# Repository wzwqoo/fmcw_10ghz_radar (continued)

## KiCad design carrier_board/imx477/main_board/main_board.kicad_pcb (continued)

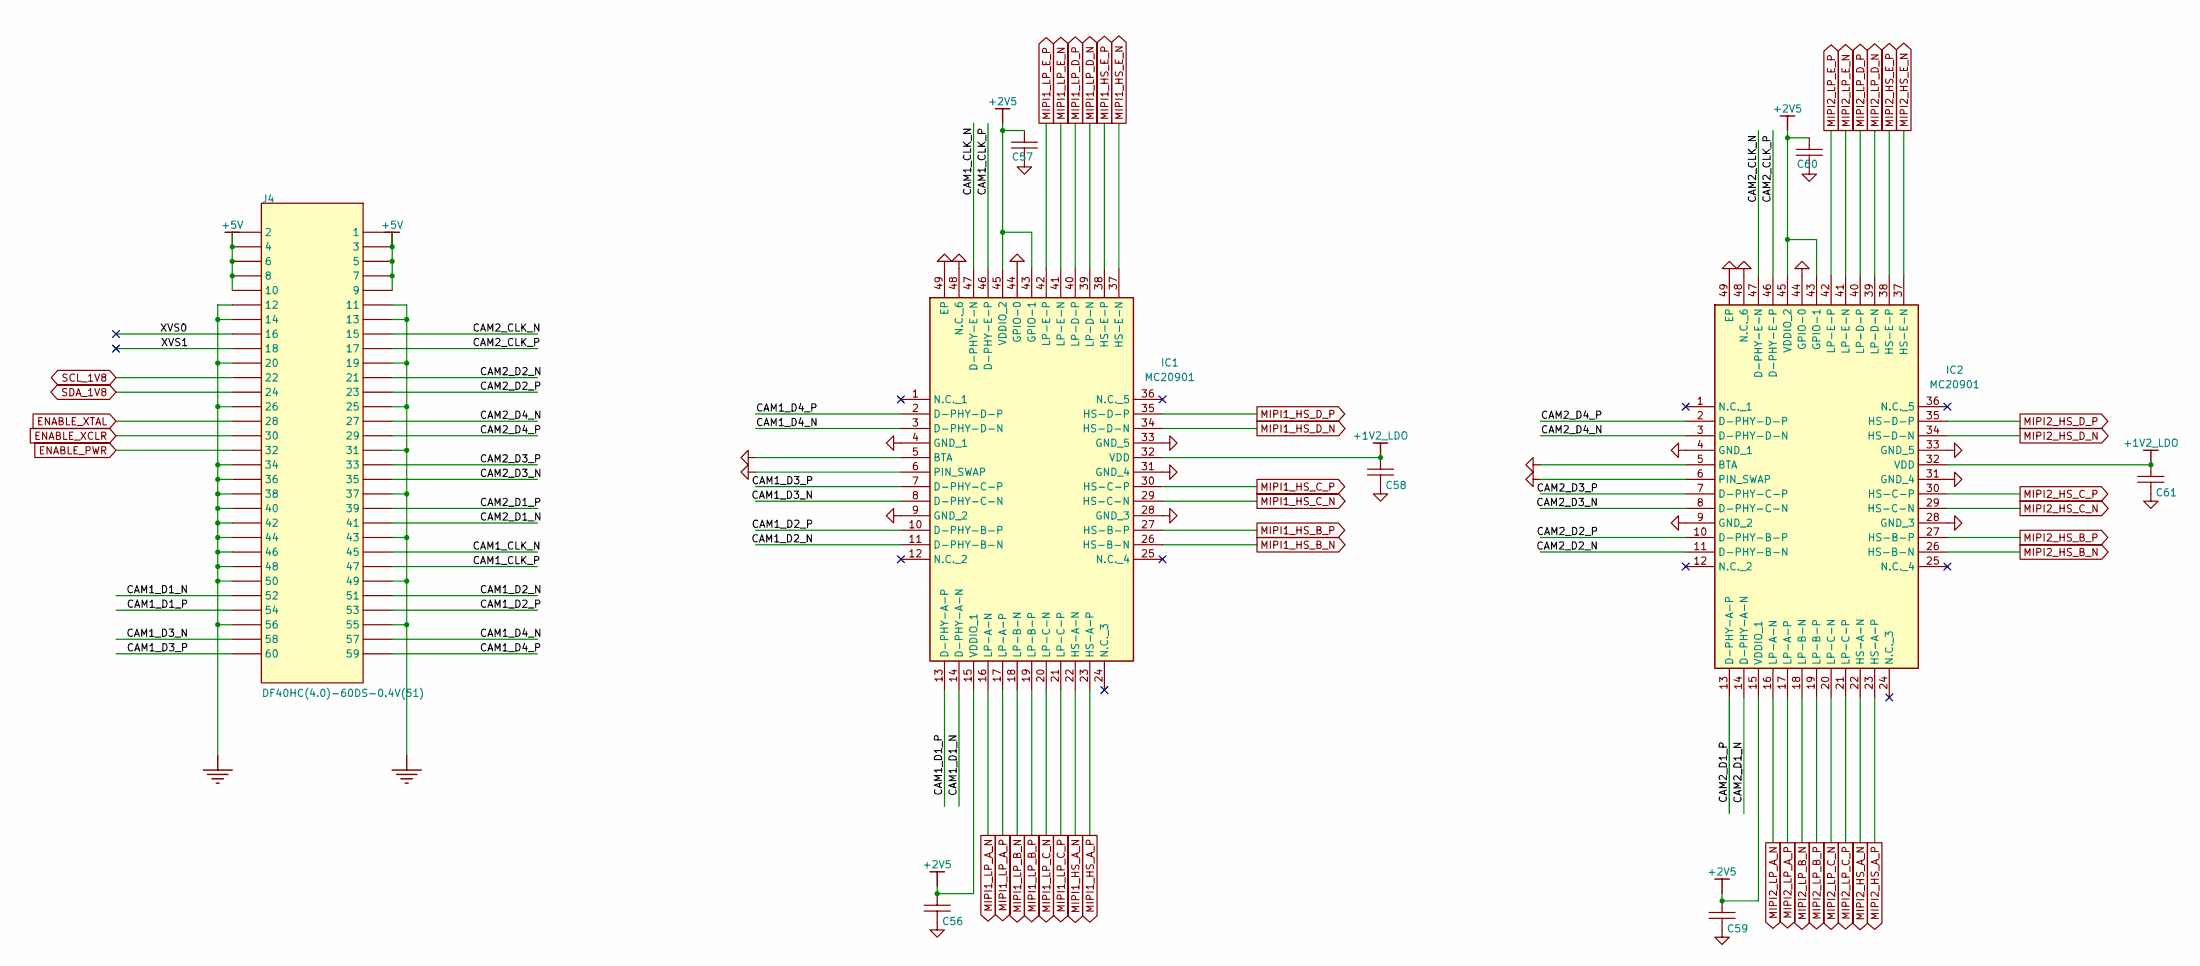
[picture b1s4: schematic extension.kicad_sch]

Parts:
C56, C57, C58, C59, C60, C61: 100nF; C_0603_1608Metric; TOLERANCE ±10%; RATINGS 16V; X7R; MANUFACTURER PART NUMBE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 CC0402KRX7R7BB103
IC1, IC2: MC20901; QFN50P700X700X80-49N-D; Manufacturer_Part_Number MC20901
J4: DF40HC(4.0)-60DS-0.4V(51); Hirose_DF40HC(4.0)-60DS-0.4V_2x30_P0.4mm

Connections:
+1V2_LDO: C58.2, C61.2, IC1.32 (VDD), IC2.32 (VDD); also elsewhere on the board
+2V5: C56.2, C57.2, C59.2, C60.2, IC1.15 (VDDIO_1), IC1.43 (GPIO-1), IC1.45 (VDDIO_2), IC2.15 (VDDIO_1), IC2.43 (GPIO-1), IC2.45 (VDDIO_2); also elsewhere on the board
+5V: J4.1, J4.2, J4.3, J4.4, J4.5, J4.6, J4.7, J4.8, J4.9, J4.10; also elsewhere on the board
/extension/CAM1_CLK_N: IC1.47 (D-PHY-E-N), J4.45
/extension/CAM1_CLK_P: IC1.46 (D-PHY-E-P), J4.47
/extension/CAM1_D1_N: IC1.14 (D-PHY-A-N), J4.52
/extension/CAM1_D1_P: IC1.13 (D-PHY-A-P), J4.54
/extension/CAM1_D2_N: IC1.11 (D-PHY-B-N), J4.51
/extension/CAM1_D2_P: IC1.10 (D-PHY-B-P), J4.53
/extension/CAM1_D3_N: IC1.8 (D-PHY-C-N), J4.58
/extension/CAM1_D3_P: IC1.7 (D-PHY-C-P), J4.60
/extension/CAM1_D4_N: IC1.3 (D-PHY-D-N), J4.57
/extension/CAM1_D4_P: IC1.2 (D-PHY-D-P), J4.59
/extension/CAM2_CLK_N: IC2.47 (D-PHY-E-N), J4.15
/extension/CAM2_CLK_P: IC2.46 (D-PHY-E-P), J4.17
/extension/CAM2_D1_N: IC2.14 (D-PHY-A-N), J4.41
/extension/CAM2_D1_P: IC2.13 (D-PHY-A-P), J4.39
/extension/CAM2_D2_N: IC2.11 (D-PHY-B-N), J4.21
/extension/CAM2_D2_P: IC2.10 (D-PHY-B-P), J4.23
/extension/CAM2_D3_N: IC2.8 (D-PHY-C-N), J4.35
/extension/CAM2_D3_P: IC2.7 (D-PHY-C-P), J4.33
/extension/CAM2_D4_N: IC2.3 (D-PHY-D-N), J4.27
/extension/CAM2_D4_P: IC2.2 (D-PHY-D-P), J4.29
/extension/XVS0: J4.16
/extension/XVS1: J4.18
ENABLE_PWR: J4.32; also elsewhere on the board
ENABLE_XCLR: J4.30; also elsewhere on the board
ENABLE_XTAL: J4.28; also elsewhere on the board
GND: C56.1, C57.1, C58.1, C59.1, C60.1, C61.1, IC1.4 (GND_1), IC1.5 (BTA), IC1.6 (PIN_SWAP), IC1.9 (GND_2), IC1.28 (GND_3), IC1.31 (GND_4), IC1.33 (GND_5), IC1.44 (GPIO-0), IC1.48 (N.C._6), IC1.49 (EP), IC2.4 (GND_1), IC2.5 (BTA), IC2.6 (PIN_SWAP), IC2.9 (GND_2), IC2.28 (GND_3), IC2.31 (GND_4), IC2.33 (GND_5), IC2.44 (GPIO-0), IC2.48 (N.C._6), IC2.49 (EP), J4.11, J4.12, J4.13, J4.14, J4.19, J4.20, J4.25, J4.26, J4.31, J4.34, J4.36, J4.37, J4.38, J4.40, J4.42, J4.43, J4.44, J4.46, J4.48, J4.49, J4.50, J4.55, J4.56; also elsewhere on the board
MIPI1_HS_A_N: IC1.22 (HS-A-N); also elsewhere on the board
MIPI1_HS_A_P: IC1.23 (HS-A-P); also elsewhere on the board
MIPI1_HS_B_N: IC1.26 (HS-B-N); also elsewhere on the board
MIPI1_HS_B_P: IC1.27 (HS-B-P); also elsewhere on the board
MIPI1_HS_C_N: IC1.29 (HS-C-N); also elsewhere on the board
MIPI1_HS_C_P: IC1.30 (HS-C-P); also elsewhere on the board
MIPI1_HS_D_N: IC1.34 (HS-D-N); also elsewhere on the board
MIPI1_HS_D_P: IC1.35 (HS-D-P); also elsewhere on the board
MIPI1_HS_E_N: IC1.37 (HS-E-N); also elsewhere on the board
MIPI1_HS_E_P: IC1.38 (HS-E-P); also elsewhere on the board
MIPI1_LP_A_N: IC1.16 (LP-A-N); also elsewhere on the board
MIPI1_LP_A_P: IC1.17 (LP-A-P); also elsewhere on the board
MIPI1_LP_B_N: IC1.18 (LP-B-N); also elsewhere on the board
MIPI1_LP_B_P: IC1.19 (LP-B-P); also elsewhere on the board
MIPI1_LP_C_N: IC1.20 (LP-C-N); also elsewhere on the board
MIPI1_LP_C_P: IC1.21 (LP-C-P); also elsewhere on the board
MIPI1_LP_D_N: IC1.39 (LP-D-N); also elsewhere on the board
MIPI1_LP_D_P: IC1.40 (LP-D-P); also elsewhere on the board
MIPI1_LP_E_N: IC1.41 (LP-E-N); also elsewhere on the board
MIPI1_LP_E_P: IC1.42 (LP-E-P); also elsewhere on the board
MIPI2_HS_A_N: IC2.22 (HS-A-N); also elsewhere on the board
MIPI2_HS_A_P: IC2.23 (HS-A-P); also elsewhere on the board
MIPI2_HS_B_N: IC2.26 (HS-B-N); also elsewhere on the board
MIPI2_HS_B_P: IC2.27 (HS-B-P); also elsewhere on the board
MIPI2_HS_C_N: IC2.29 (HS-C-N); also elsewhere on the board
MIPI2_HS_C_P: IC2.30 (HS-C-P); also elsewhere on the board
MIPI2_HS_D_N: IC2.34 (HS-D-N); also elsewhere on the board
MIPI2_HS_D_P: IC2.35 (HS-D-P); also elsewhere on the board
MIPI2_HS_E_N: IC2.37 (HS-E-N); also elsewhere on the board
MIPI2_HS_E_P: IC2.38 (HS-E-P); also elsewhere on the board
MIPI2_LP_A_N: IC2.16 (LP-A-N); also elsewhere on the board
MIPI2_LP_A_P: IC2.17 (LP-A-P); also elsewhere on the board
MIPI2_LP_B_N: IC2.18 (LP-B-N); also elsewhere on the board
MIPI2_LP_B_P: IC2.19 (LP-B-P); also elsewhere on the board
MIPI2_LP_C_N: IC2.20 (LP-C-N); also elsewhere on the board
MIPI2_LP_C_P: IC2.21 (LP-C-P); also elsewhere on the board
MIPI2_LP_D_N: IC2.39 (LP-D-N); also elsewhere on the board
MIPI2_LP_D_P: IC2.40 (LP-D-P); also elsewhere on the board
MIPI2_LP_E_N: IC2.41 (LP-E-N); also elsewhere on the board
MIPI2_LP_E_P: IC2.42 (LP-E-P); also elsewhere on the board
SCL_1V8: J4.22
SDA_1V8: J4.24

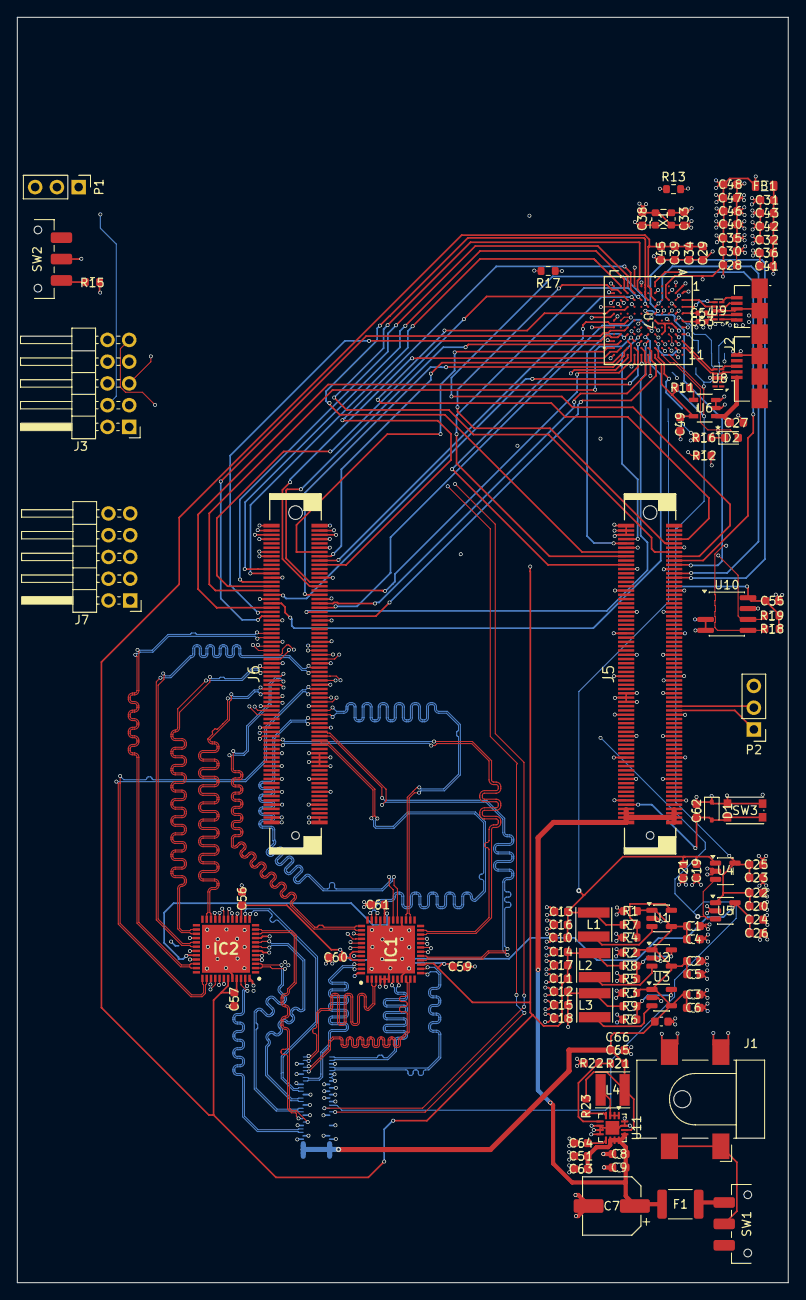
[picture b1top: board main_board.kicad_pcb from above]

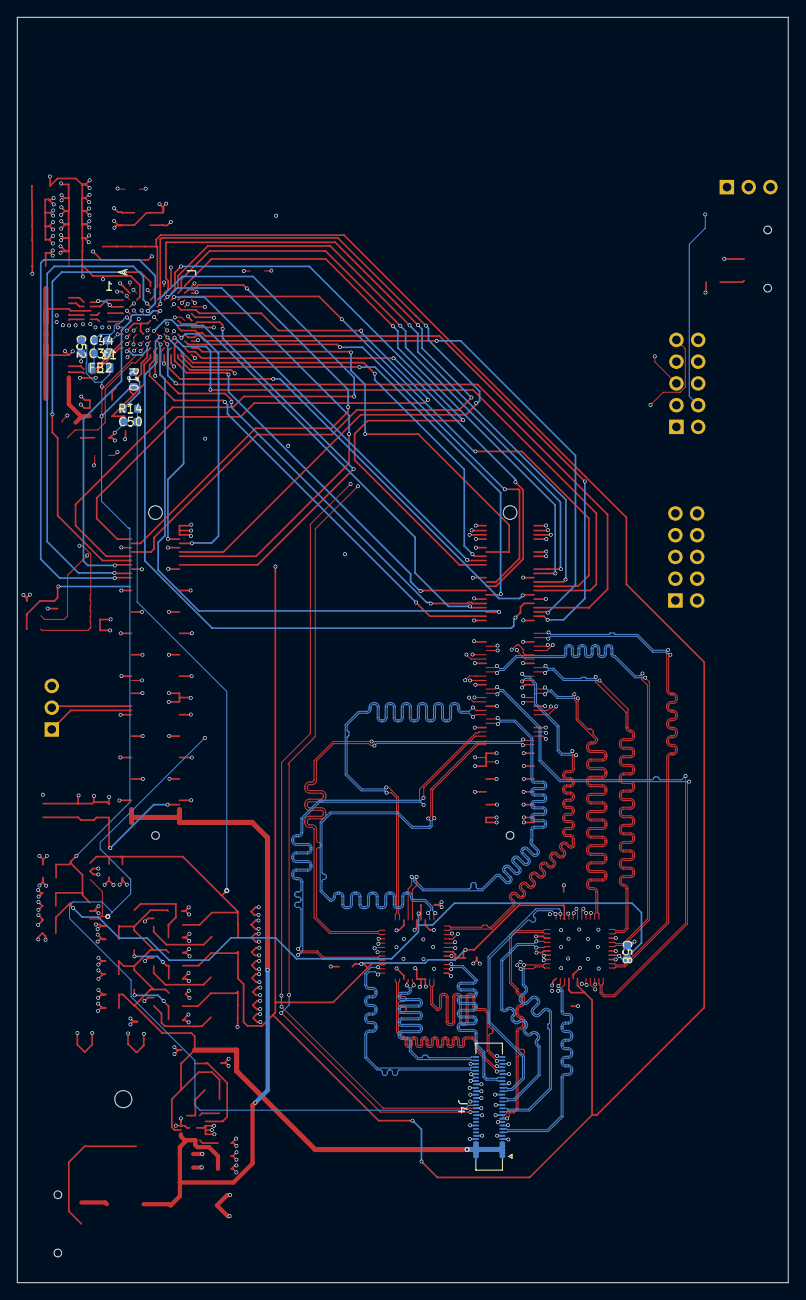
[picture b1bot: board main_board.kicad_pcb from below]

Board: 6 copper layers, 90.0 x 147.7 mm, 123 parts (9 on the bottom side), 165 nets.

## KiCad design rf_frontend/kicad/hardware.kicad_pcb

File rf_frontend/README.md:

# `rf_frontend/` — 10 GHz 1TX/3RX FMCW front-end

The analog half of the platform: a coherent FMCW radar that sweeps 192 MHz
around 10 GHz in 108 µs, radiates it from a series-fed patch column, and lands
three receive chains on an ADAR7251's simultaneously-sampled ADC channels.
Simultaneous sampling is the point — it is what preserves the inter-receiver
phase that angle-of-arrival and the spin-axis interferometer downstream consume.

Everything is discrete MMIC rather than an integrated transceiver, so each
channel's gain, noise figure and LO drive is set and measurable on its own.

## Signal chain

```
                     ┌──────────────┐
  KT2520K ──ref──►   │   ADF4159    │  fractional-N ramp PLL, type 2
                     │  ramp gen +  │──── CP ──► ADA4625-1 loop filter ──┐
                     │     PFD      │                                    │
                     └──────▲───────┘                                    ▼
                            │ ÷2 output (feedback only)          ┌──────────────┐
                            └────────────────────────────────────│   HMC1163    │
                                                                 │ 10 GHz VCO   │
                                                                 └──────┬───────┘
                                                        11 dBm fundamental
                                                                        │
                                        ┌───────── 4 dB branchline coupler ─────────┐
                                        │                                           │
                              TX patch column                          1 → 3 Wilkinson tree
                                (+7 dBm radiated)                       │      │      │
                                                                        ▼      ▼      ▼
     RX column ×3 ──► PMA3-14LN+ ──► LTC5548 ◄──────────────────────── LO (≈0 dBm at each mixer)
                       (+22.6 dB)      │
                                       ▼
                                  ADA4940-2 differential IF driver ──► ADAR7251 (4 ch, 16-bit)
```

Key consequence of the LNA-first ordering: the LNA contributes no line of its
own to the link budget — it lifts signal and noise together — but it is why the
cascaded noise figure is ≈2 dB rather than the ≈12 dB of a mixer-first chain.
The LTC5548's ≈8.5 dB conversion loss enters only as added noise, divided down
by the LNA gain.

## Key components

| Function | Part |
|---|---|
| Ramp PLL (fractional-N, type 2) | ADF4159 |
| VCO, 10 GHz fundamental + ÷2 | HMC1163 |
| Loop-filter amplifier (JFET input) | ADA4625-1 |
| Reference oscillator / buffer | KT2520K, NB3N551 |
| LNA, ×3 | PMA3-14LN+ |
| Downconversion mixer, ×3 | LTC5548 |
| Differential IF driver | ADA4940-2 |
| ADC — 4 channels, simultaneous sampling | ADAR7251 |
| LO distribution | 4 dB branchline coupler + 1→3 Wilkinson splitter (both distributed, on-board) |
| Pad attenuators | PAT1220 (4 dB / 6 dB) |
| Supplies | TPS7A4701 and TPS7A91 (low-noise LDO for the RF rails), TPS54302, MIC29302A, ADP1613 boost |
| Host interface | 40-pin shielded FPC to the carrier board |

## Antenna array

Three receive columns plus one transmit column, all series-fed patches on the
top layer:

- **Series-fed columns, not single patches.** On this substrate a lone patch
  radiates poorly at 10 GHz; an 8-element column reaches ≈15.5 dBi directivity
  and ≈8.5 dBi realized gain at ≈18% radiation efficiency, so the column's
  directivity buys back most of what the dielectric burns as heat.
- **Staggered "^" geometry.** Adjacent phase centres are stepped λ/2 (15 mm) in
  *both* array axes, so neither measured adjacent-pair phase ever wraps, and
  their sum supplies a full-λ baseline whose ambiguity is already spent. The
  solve stays unambiguous across ±90° on both principal axes.
- **TX–RX separation of 75 mm** — simultaneously the isolation the array needs
  and the largest separation the LO trace-loss budget allows.

## Substrate

Isola 370HR, Dk 3.92, tanδ 0.025, 0.254 mm dielectric. It is a lossy laminate
for X-band, chosen deliberately over a PTFE alternative on cost; the antenna
design in `ads/` is what makes it work rather than the substrate.

## Layout

| Path | Contents |
|---|---|
| `kicad/hardware.kicad_pro`, `hardware.kicad_sch` | KiCad project and top-level sheet |
| `kicad/TX.kicad_sch` | VCO, ramp PLL, loop filter, coupler, LO tree, TX feed |
| `kicad/RX.kicad_sch` | 3× LNA → mixer receive chains |
| `kicad/IF.kicad_sch` | IF conditioning and the ADAR7251 |
| `kicad/power.kicad_sch` | Power tree, with the RF rails on low-noise LDOs |
| `kicad/hardware.kicad_pcb` | Board layout |
| `kicad/Design1.pll`, `Design2.pll` | ADIsimPLL loop designs |
| `kicad/footprints/` | Project-local libraries — including the hand-drawn `antenna`, `splitter` and `branchline` distributed structures |
| `ads/` | Momentum results (see below) |
| `figures/` | Link budget, array spacing / precision, near-field analysis, board render |

The distributed structures are *footprints*, not components: the patch column,
the Wilkinson splitter and the branchline coupler are drawn as copper in
`kicad/footprints/*.pretty` and placed like parts.

## EM verification (`ads/`)

Each on-board distributed structure was simulated in ADS/Momentum on the 370HR
stackup before being committed to copper. The workspace itself is too large to
track, so each result is captured as an image:

| File | Result |
|---|---|
| `patch_antenna.png`, `patch_antenna_schema.png`, `patch_antenna_result.png` | The series-fed column: geometry, feed schema, and realized gain / efficiency |
| `splitter_result.png` | 1→3 Wilkinson tree, per-port split and match |
| `coupler_result.png` | 4 dB branchline coupler |
| `LO_tree.png`, `LO_tree_result.png` | The assembled coupler + splitter LO distribution — ≈0 dBm landing at each mixer, −11 dB worst-case tree loss from the 11 dBm VCO |
| `LNA_gain.png` | Receive-chain gain |
| `TX_RX_isolation.png` | ≈−60 dB against a −30 dB requirement |
| `3RX_coupling.png` | Adjacent-RX coupling of −35 to −45 dB, which bounds worst-case angle-of-arrival error below 0.5° |

## Opening the board

```
kicad rf_frontend/kicad/hardware.kicad_pro     # KiCad 8 or newer
```

The render at the top of this page was produced with `kicad-cli pcb render`.

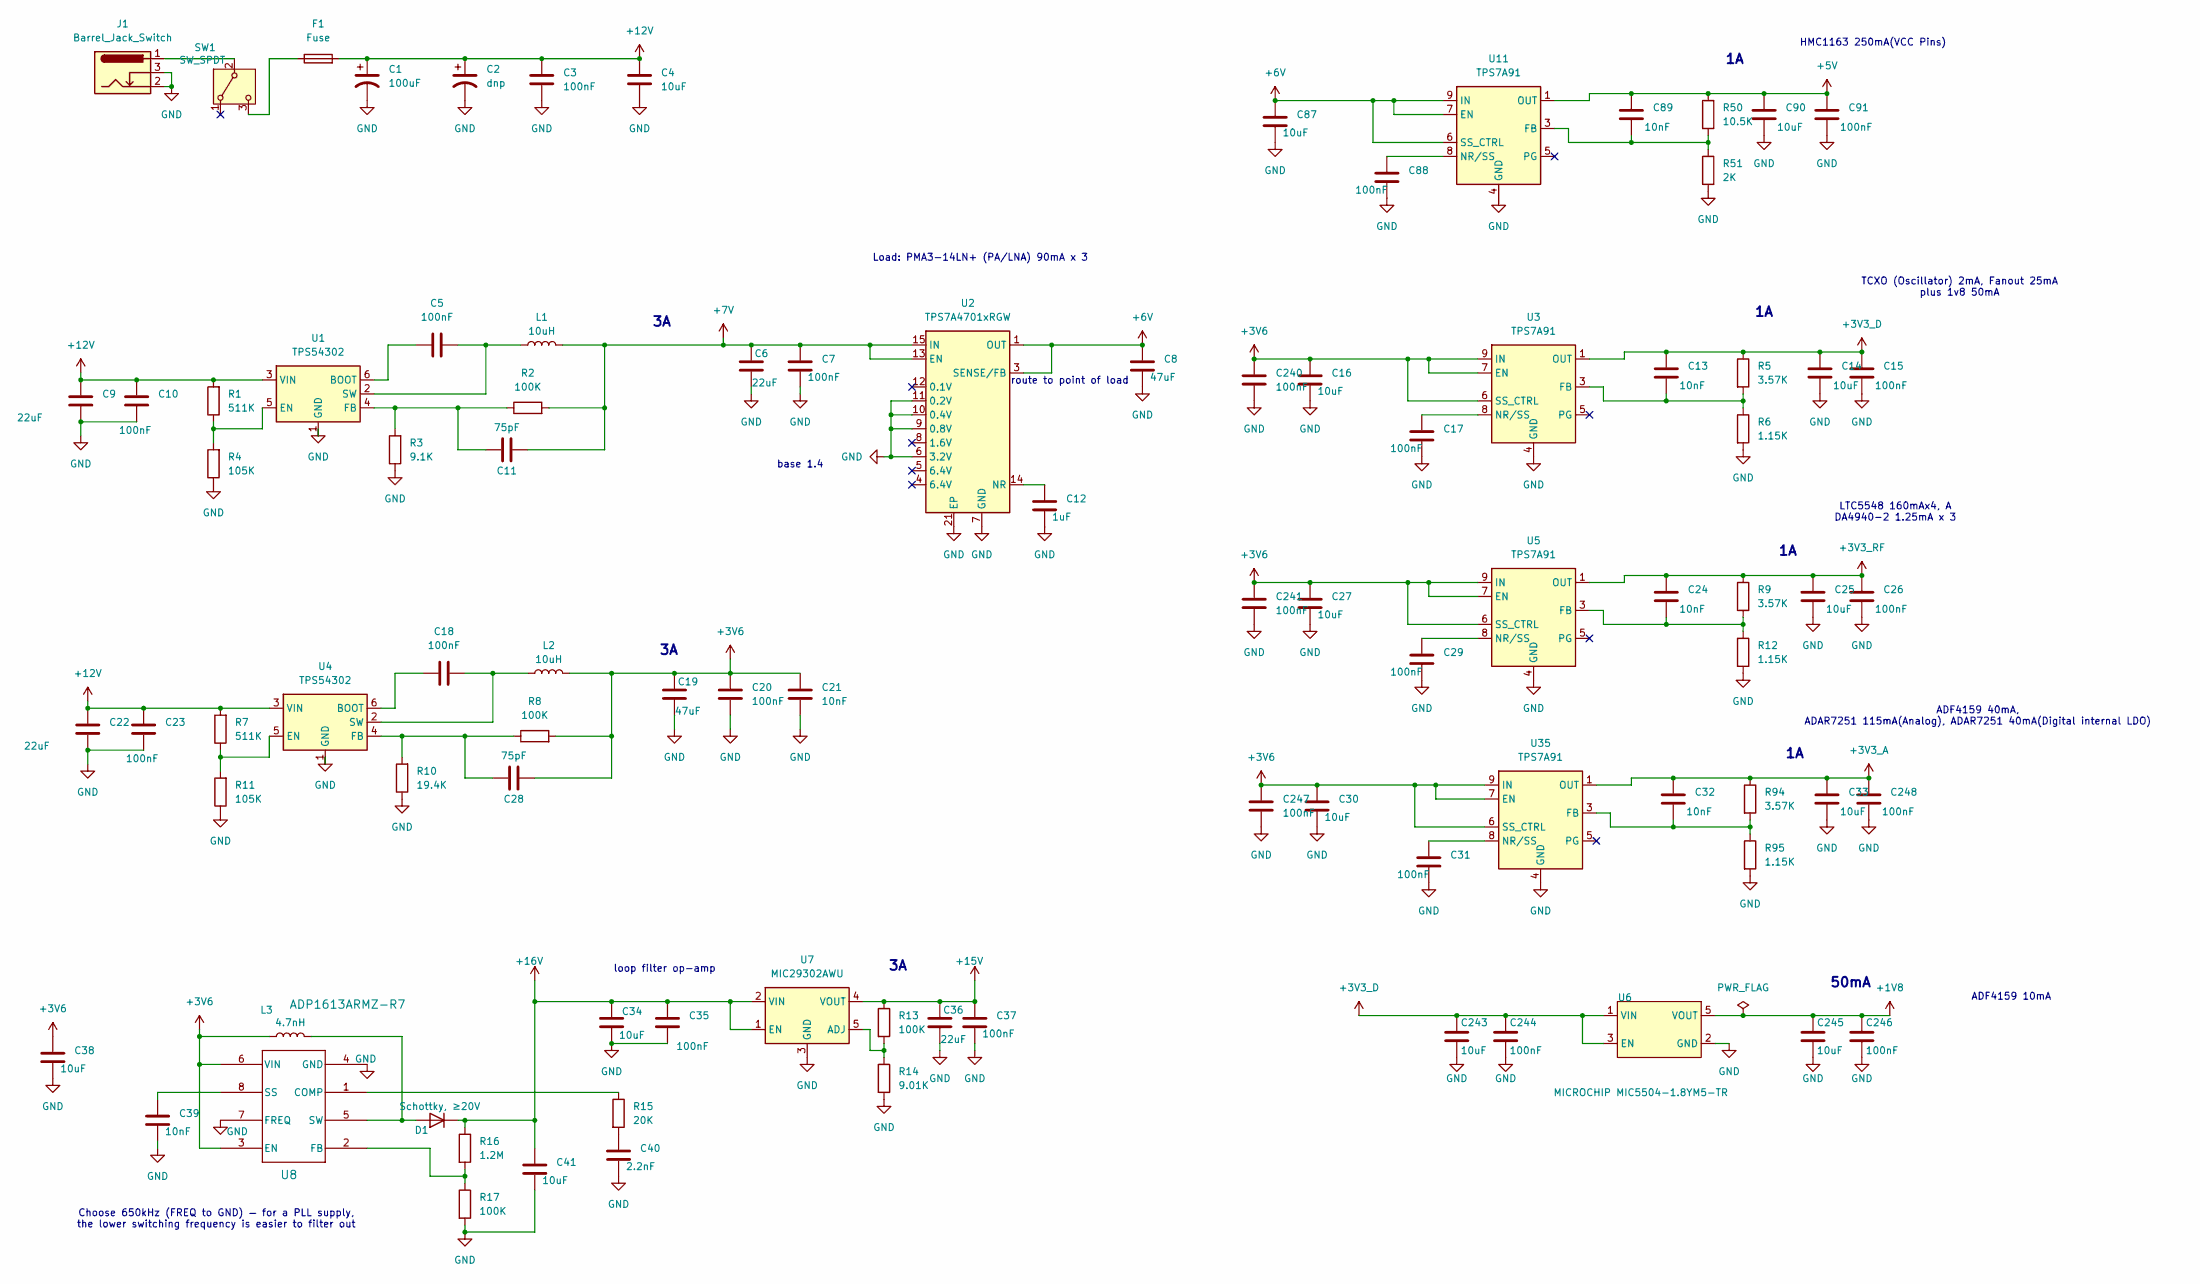
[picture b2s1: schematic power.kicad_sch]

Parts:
C1: 100uF; CAPC6153X670N
C2: dnp; CAPC6153X670N
C3, C5, C7, C10, C15, C17, C18, C20, C23, C26, C29, C31, C35, C37, C88, C91, C240, C241, C244, C246, C247, C248: 100nF; C_0402_1005Metric
C4, C14, C16, C25, C27, C30, C33, C34, C38, C41, C243, C245: 10uF; C_0805_2012Metric
C6, C9, C22, C36: 22uF; C_0805_2012Metric
C8, C19: 47uF; C_0805_2012Metric
C11, C28: 75pF; C_0402_1005Metric
C12: 1uF; C_0402_1005Metric
C13, C21, C24, C32, C39, C89: 10nF; C_0402_1005Metric
C40: 2.2nF; C_0402_1005Metric
C87, C90: 10uF; C_0402_1005Metric
D1: Schottky, ≥20V; D_SMA
F1: Fuse; Fuse_0603_1608Metric; LCSC Part # SMD1812P200TF16
J1: Barrel_Jack_Switch; BarrelJack_CUI_PJ-063AH_Horizontal
L1, L2: 10uH; L_Sunlord_MWSA0602S; Part# FXL0630-100-M
L3: 4.7nH; L_0402_1005Metric
R1, R7: 511K; R_0402_1005Metric
R2, R8, R13, R17: 100K; R_0402_1005Metric
R3: 9.1K; R_0402_1005Metric
R4, R11: 105K; R_0402_1005Metric
R5, R9, R94: 3.57K; R_0402_1005Metric
R6, R12, R95: 1.15K; R_0402_1005Metric
R10: 19.4K; R_0402_1005Metric
R14: 9.01K; R_0402_1005Metric
R15: 20K; R_0402_1005Metric
R16: 1.2M; R_0402_1005Metric
R50: 10.5K; R_0402_1005Metric
R51: 2K; R_0402_1005Metric
SW1: SW_SPDT; SW_SPDT_CK_JS102011SAQN; Part# JS102011SAQN; LCSC Part # C221660
U1, U4: TPS54302; SOT-23-6
U2: TPS7A4701xRGW; Texas_RGW0020A_VQFN-20-1EP_5x5mm_P0.65mm_EP3.15x3.15mm
U3, U5, U11, U35: TPS7A91; Texas_S-PDSO-N10_EP1.2x2mm
U6: MICROCHIP MIC5504-1.8YM5-TR; SOT-23-5; Part# MIC5504-1.8YM5-TR; LCSC Part # C626116
U7: MIC29302AWU; TO-263-5_TabPin3
U8: ADP1613ARMZ-R7; MSOP-8-1EP_3x3mm_P0.65mm_EP1.5x1.8mm

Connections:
+1V8: C245.1, C246.1, U6.5 (VOUT); also elsewhere on the board
+3V3_A: C32.1, C33.1, C248.1, R94.1, U35.1 (OUT), U35.2 (OUT); also elsewhere on the board
+3V3_D: C13.1, C14.1, C15.1, C243.1, C244.1, R5.1, U3.1 (OUT), U3.2 (OUT), U6.1 (VIN), U6.3 (EN); also elsewhere on the board
+3V3_RF: C24.1, C25.1, C26.1, R9.1, U5.1 (OUT), U5.2 (OUT); also elsewhere on the board
+3V6: C16.1, C19.1, C20.1, C21.1, C27.1, C28.2, C30.1, C38.1, C240.1, C241.1, C247.1, L2.2, L3.1, R8.2, U3.6 (SS_CTRL), U3.7 (EN), U3.9 (IN), U3.10 (IN), U5.6 (SS_CTRL), U5.7 (EN), U5.9 (IN), U5.10 (IN), U8.3 (EN), U8.6 (VIN), U35.6 (SS_CTRL), U35.7 (EN), U35.9 (IN), U35.10 (IN)
+5V: C89.1, C90.1, C91.1, R50.1, U11.1 (OUT), U11.2 (OUT); also elsewhere on the board
+6V: C8.1, C87.1, U2.1 (OUT), U2.3 (SENSE/FB), U2.20 (OUT), U11.6 (SS_CTRL), U11.7 (EN), U11.9 (IN), U11.10 (IN); also elsewhere on the board
+7V: C6.1, C7.1, C11.2, L1.2, R2.2, U2.13 (EN), U2.15 (IN), U2.16 (IN)
+12V: C1.1, C2.1, C3.1, C4.1, C9.1, C10.1, C22.1, C23.1, F1.2, R1.2, R7.2, U1.3 (VIN), U4.3 (VIN)
+15V: C36.1, C37.1, R13.1, U7.4 (VOUT); also elsewhere on the board
+16V: C34.1, C35.1, C41.1, D1.1 (K), R16.1, U7.1 (EN), U7.2 (VIN)
GND: C1.2, C2.2, C3.2, C4.2, C6.2, C7.2, C8.2, C9.2, C10.2, C12.2, C14.2, C15.2, C16.2, C17.2, C19.2, C20.2, C21.2, C22.2, C23.2, C25.2, C26.2, C27.2, C29.2, C30.2, C31.2, C33.2, C34.2, C35.2, C36.2, C37.2, C38.2, C39.2, C40.2, C41.2, C87.2, C88.2, C90.2, C91.2, C240.2, C241.2, C243.2, C244.2, C245.2, C246.2, C247.2, C248.2, J1.2, J1.3, R3.1, R4.1, R6.2, R10.1, R11.1, R12.2, R14.2, R17.2, R51.2, R95.2, U1.1 (GND), U2.6 (3.2V), U2.7 (GND), U2.9 (0.8V), U2.10 (0.4V), U2.11 (0.2V), U2.21 (EP), U3.4 (GND), U3.11 (GND), U4.1 (GND), U5.4 (GND), U5.11 (GND), U6.2 (GND), U7.3 (GND), U8.4 (GND), U8.7 (FREQ), U8.9, U11.4 (GND), U11.11 (GND), U35.4 (GND), U35.11 (GND); also elsewhere on the board
unnamed: C40.1, R15.2
unnamed: D1.2 (A), L3.2, U8.5 (SW)
unnamed: J1.1, SW1.2 (B)
unnamed: F1.1, SW1.3 (C)
unnamed: C5.1, U1.6 (BOOT)
unnamed: R1.1, R4.2, U1.5 (EN)
unnamed: C11.1, R2.1, R3.2, U1.4 (FB)
unnamed: C5.2, L1.1, U1.2 (SW)
unnamed: C12.1, U2.14 (NR)
unnamed: C13.2, R5.2, R6.1, U3.3 (FB)
unnamed: C17.1, U3.8 (NR/SS)
unnamed: C18.1, U4.6 (BOOT)
unnamed: R7.1, R11.2, U4.5 (EN)
unnamed: C28.1, R8.1, R10.2, U4.4 (FB)
unnamed: C18.2, L2.1, U4.2 (SW)
unnamed: C24.2, R9.2, R12.1, U5.3 (FB)
unnamed: C29.1, U5.8 (NR/SS)
unnamed: R13.2, R14.1, U7.5 (ADJ)
unnamed: R15.1, U8.1 (COMP)
unnamed: R16.2, R17.1, U8.2 (FB)
unnamed: C39.1, U8.8 (SS)
unnamed: C89.2, R50.2, R51.1, U11.3 (FB)
unnamed: C88.1, U11.8 (NR/SS)
unnamed: C32.2, R94.2, R95.1, U35.3 (FB)
unnamed: C31.1, U35.8 (NR/SS)

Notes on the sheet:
ADF4159 10mA
route to point of load
TCXO (Oscillator) 2mA, Fanout 25mA plus 1v8 50mA
Load: PMA3-14LN+ (PA/LNA) 90mA x 3
base 1.4
50mA
loop filter op-amp
LTC5548 160mAx4, A DA4940-2 1.25mA x 3
Choose 650kHz (FREQ to GND) — for a PLL supply, the lower switching frequency is easier to filter out
ADF4159 40mA, ADAR7251 115mA(Analog), ADAR7251 40mA(Digital internal LDO)
HMC1163 250mA(VCC Pins)
